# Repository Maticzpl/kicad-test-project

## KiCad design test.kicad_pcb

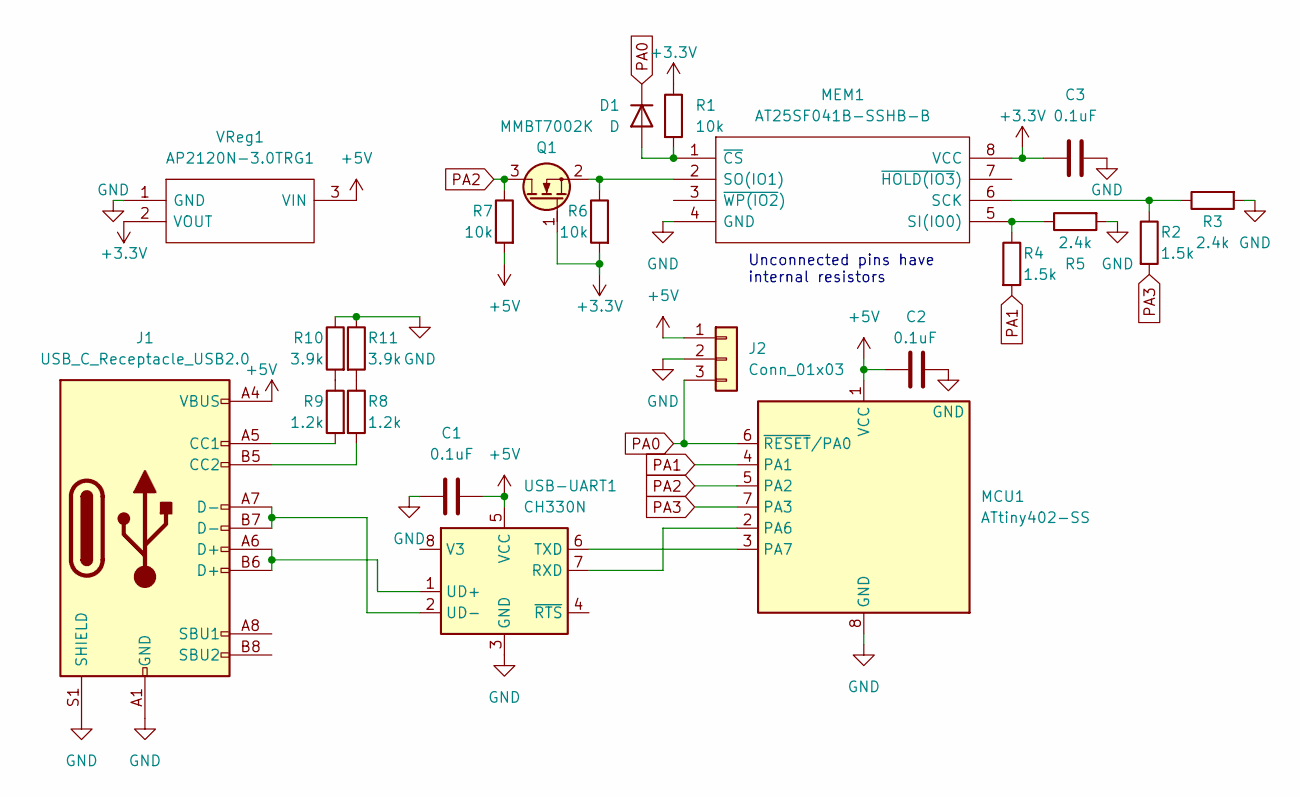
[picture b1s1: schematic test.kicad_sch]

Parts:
C1, C3: 0.1uF; C_0805_2012Metric_Pad1.18x1.45mm_HandSolder
C2: 0.1uF; C_0805_2012Metric
D1: D; D_0805_2012Metric
J1: USB_C_Receptacle_USB2.0; USB4110GFA_S
J2: Conn_01x03; PinHeader_1x03_P2.54mm_Vertical
MCU1: ATtiny402-SS; SOIC-8_3.9x4.9mm_P1.27mm
MEM1: AT25SF041B-SSHB-B; SOIC127P600X175-8N; Manufacturer_Part_Number AT25SF041B-SSHB-B; Mouser Part Number 988-AT25SF041-SSH-B
Q1: MMBT7002K; SOT-23
R1, R6, R7: 10k; R_0805_2012Metric
R2, R4: 1.5k; R_0805_2012Metric
R3, R5: 2.4k; R_0805_2012Metric
R8, R9: 1.2k; R_0805_2012Metric
R10, R11: 3.9k; R_0805_2012Metric
USB-UART1: CH330N; SOIC-8_3.9x4.9mm_P1.27mm
VReg1: AP2120N-3.0TRG1; SOT96P240X120-3N; Manufacturer_Part_Number AP2120N-3.0TRG1; Mouser Part Number 621-AP2120N-3.0TRG1

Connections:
+3.3V: C3.1, MEM1.8 (VCC), Q1.1 (G), R1.1, R6.2, VReg1.2 (VOUT)
+5V: C1.2, C2.1, J1.A4 (VBUS), J1.A9 (VBUS), J1.B4 (VBUS), J1.B9 (VBUS), J2.1, MCU1.1 (VCC), R7.2, USB-UART1.5 (VCC), VReg1.3 (VIN)
GND: C1.1, C2.2, C3.2, J1.A1 (GND), J1.A12 (GND), J1.B1 (GND), J1.B12 (GND), J1.S1 (SHIELD), J2.2, MCU1.8 (GND), MEM1.4 (GND), R3.2, R5.2, R10.1, R11.1, USB-UART1.3 (GND), VReg1.1 (GND)
unnamed: D1.2 (A), MEM1.1 (~CS), R1.2
unnamed: J1.A5 (CC1), R9.2
unnamed: J1.B5 (CC2), R8.2
unnamed: MCU1.2 (PA6), USB-UART1.7 (RXD)
unnamed: MCU1.3 (PA7), USB-UART1.6 (TXD)
unnamed: MEM1.6 (SCK), R2.1, R3.1
unnamed: MEM1.5 (SI(IO0)), R4.1, R5.1
unnamed: MEM1.2 (SO(IO1)), Q1.2 (S), R6.1
unnamed: R9.1, R10.2
unnamed: R8.1, R11.2
unnamed: J1.A6 (D+), J1.B6 (D+), USB-UART1.1 (UD+)
unnamed: J1.A7 (D-), J1.B7 (D-), USB-UART1.2 (UD-)
PA0: D1.1 (K), J2.3, MCU1.6 (~RESET/PA0)
PA1: MCU1.4 (PA1), R4.2
PA2: MCU1.5 (PA2), Q1.3 (D), R7.1
PA3: MCU1.7 (PA3), R2.2

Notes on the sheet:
Unconnected pins have internal resistors

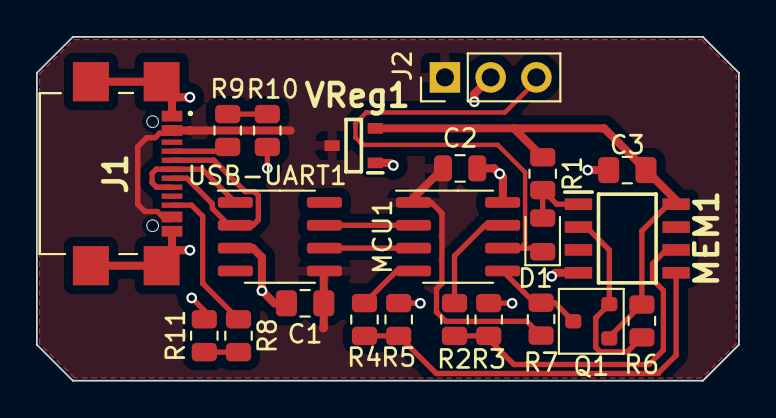
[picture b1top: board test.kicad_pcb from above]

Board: 2 copper layers, 39.0 x 19.1 mm, 22 parts (0 on the bottom side), 19 nets.

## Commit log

2023-12-12 init
2023-12-12 update gitignore
2023-12-12 Rerouted with bigger traces, default usb receptacle symbol
2023-12-12 Programming pins
